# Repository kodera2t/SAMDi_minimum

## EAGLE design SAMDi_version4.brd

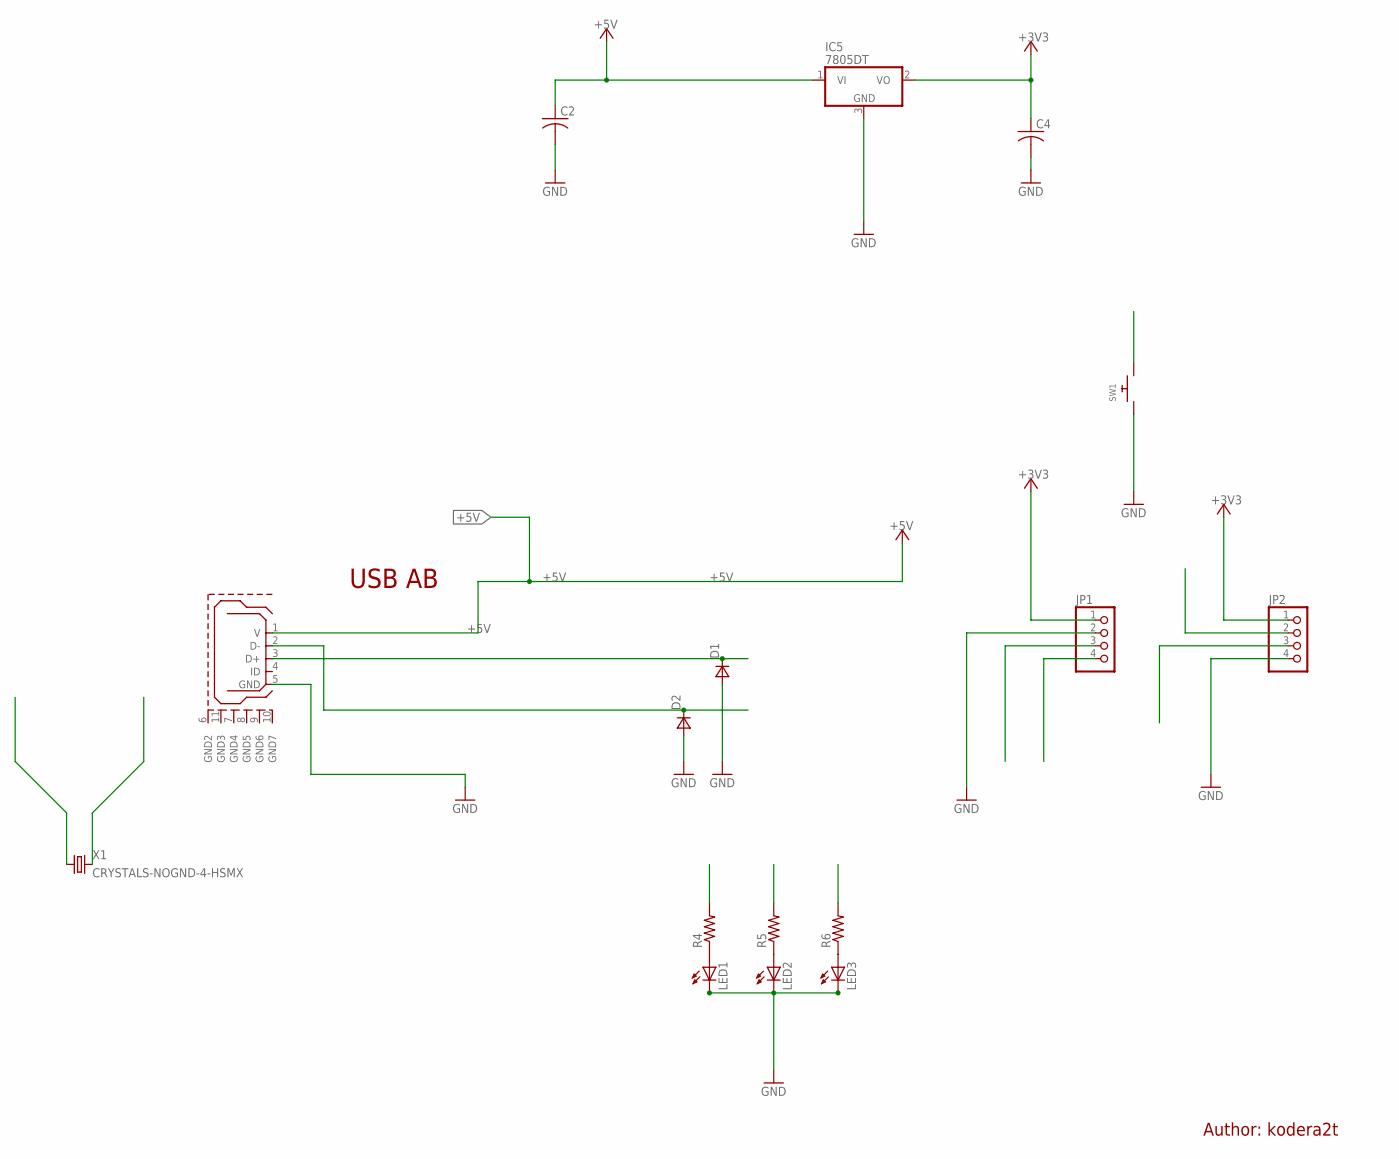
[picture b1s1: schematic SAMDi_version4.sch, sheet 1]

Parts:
C2, C4: C-USC0603; C0603
D1, D2: DSOD323; SOD323
IC5: 7805DT; TO252
JP1: HEADER-1X4; 1X04_OVAL
JP2: PINHD-1X4; 1X04
LED1, LED2, LED3: LEDCHIP-LED0603; CHIP-LED0603
R4, R5, R6: R-US_R0603; R0603
SW1: SWITCH_PUSHBUTTONSOFTTOUCHSMD_SJ; PUSHBUTTON_SMD_SJ
U$1: USB_MICROB; USB_MICROB_PACKAGE
X1: CRYSTALS-NOGND-4-HSMX; HC49-4-HSMX

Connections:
+3V3: C4.1, IC5.2 (VO), JP1.1, JP2.1; also elsewhere on the board
+5V: C2.1, IC5.1 (VI), U$1.1 (V)
GND: C2.2, C4.2, D1.2 (A), D2.2 (A), IC5.3 (GND), JP1.2, JP2.4, LED1.C, LED2.C, LED3.C, SW1.P$1, U$1.5 (GND); also elsewhere on the board
LED1: R4.2; also elsewhere on the board
LED2: R5.2; also elsewhere on the board
LED3: R6.2; also elsewhere on the board
unnamed: LED1.A, R4.1
unnamed: LED2.A, R5.1
unnamed: LED3.A, R6.1
RX: JP2.3; also elsewhere on the board
SCL: JP1.3; also elsewhere on the board
SDA: JP1.4; also elsewhere on the board
SWITCH1: SW1.P$2; also elsewhere on the board
TARGET_USB_N: D2.1 (C), U$1.2 (D-); also elsewhere on the board
TARGET_USB_P: D1.1 (C), U$1.3 (D+); also elsewhere on the board
TX: JP2.2; also elsewhere on the board
XTAL11: X1.2; also elsewhere on the board
XTAL22: X1.1; also elsewhere on the board

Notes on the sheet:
USB AB
Author: kodera2t

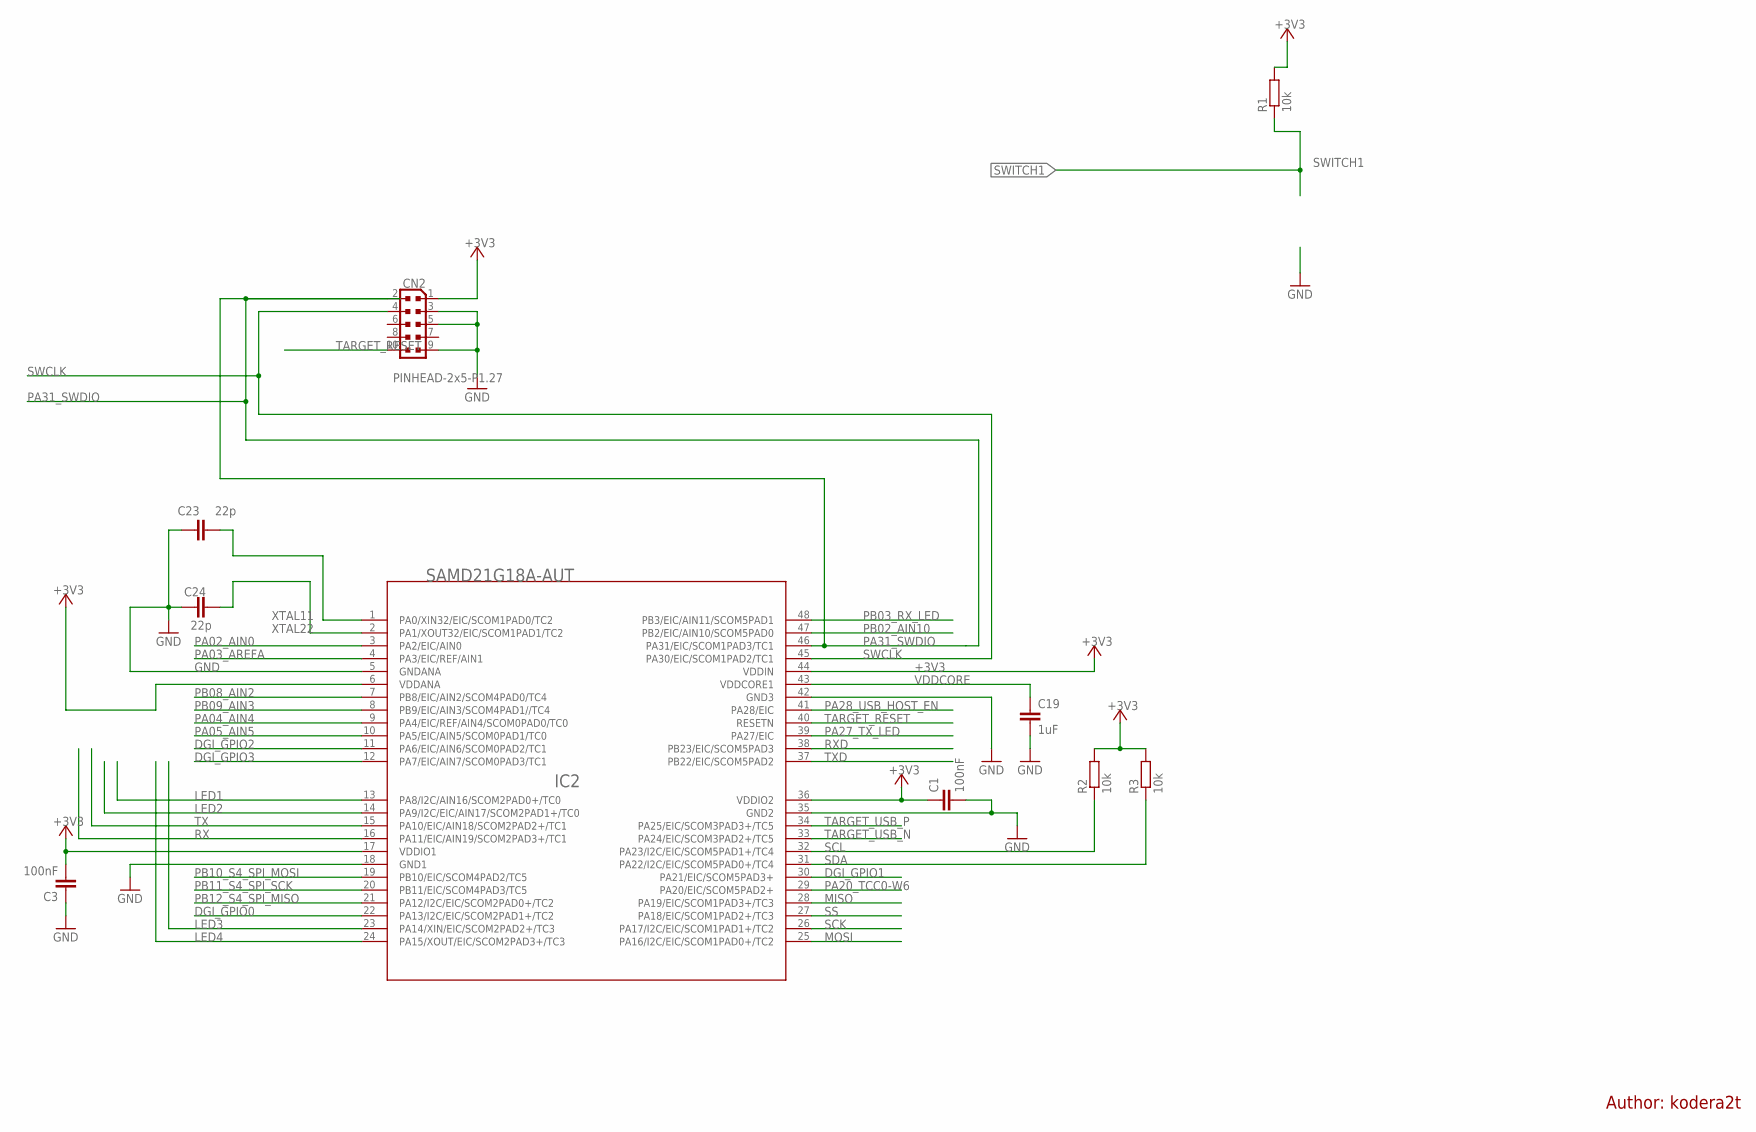
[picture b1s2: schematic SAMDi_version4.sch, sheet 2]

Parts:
C1, C3: 100nF; C0603-ROUND
C19: 1uF; C0603-ROUND
C23, C24: 22p; C0603-ROUND
CN2: PINHEAD-2x5-P1.27; PINHEAD_2X05_127
IC2: SAMD21G18A-AUT; TQFP48-7X7
R1, R2, R3: 10k; R0603-ROUND

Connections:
+3V3: C1.1, C3.2, CN2.1, IC2.6 (VDDANA), IC2.17 (VDDIO1), IC2.36 (VDDIO2), IC2.44 (VDDIN), R1.2, R2.2, R3.2; also elsewhere on the board
DGI_GPIO0: IC2.22 (PA13/I2C/EIC/SCOM2PAD1+/TC2)
DGI_GPIO1: IC2.30 (PA21/EIC/SCOM5PAD3+)
DGI_GPIO2: IC2.11 (PA6/EIC/AIN6/SCOM0PAD2/TC1)
DGI_GPIO3: IC2.12 (PA7/EIC/AIN7/SCOM0PAD3/TC1)
GND: C1.2, C3.1, C19.2, C23.1, C24.1, CN2.3, CN2.5, CN2.9, IC2.5 (GNDANA), IC2.18 (GND1), IC2.35 (GND2), IC2.42 (GND3); also elsewhere on the board
LED1: IC2.13 (PA8/I2C/AIN16/SCOM2PAD0+/TC0); also elsewhere on the board
LED2: IC2.14 (PA9/I2C/EIC/AIN17/SCOM2PAD1+/TC0); also elsewhere on the board
LED3: IC2.23 (PA14/XIN/EIC/SCOM2PAD2+/TC3); also elsewhere on the board
LED4: IC2.24 (PA15/XOUT/EIC/SCOM2PAD3+/TC3)
MISO: IC2.28 (PA19/EIC/SCOM1PAD3+/TC3)
MOSI: IC2.25 (PA16/I2C/EIC/SCOM1PAD0+/TC2)
PA02_AIN0: IC2.3 (PA2/EIC/AIN0)
PA03_AREFA: IC2.4 (PA3/EIC/REF/AIN1)
PA04_AIN4: IC2.9 (PA4/EIC/REF/AIN4/SCOM0PAD0/TC0)
PA05_AIN5: IC2.10 (PA5/EIC/AIN5/SCOM0PAD1/TC0)
PA20_TCC0-W6: IC2.29 (PA20/EIC/SCOM5PAD2+)
PA27_TX_LED: IC2.39 (PA27/EIC)
PA28_USB_HOST_EN: IC2.41 (PA28/EIC)
PA31_SWDIO: CN2.2, IC2.46 (PA31/EIC/SCOM1PAD3/TC1)
PB02_AIN10: IC2.47 (PB2/EIC/AIN10/SCOM5PAD0)
PB03_RX_LED: IC2.48 (PB3/EIC/AIN11/SCOM5PAD1)
PB08_AIN2: IC2.7 (PB8/EIC/AIN2/SCOM4PAD0/TC4)
PB09_AIN3: IC2.8 (PB9/EIC/AIN3/SCOM4PAD1//TC4)
PB10_S4_SPI_MOSI: IC2.19 (PB10/EIC/SCOM4PAD2/TC5)
PB11_S4_SPI_SCK: IC2.20 (PB11/EIC/SCOM4PAD3/TC5)
PB12_S4_SPI_MISO: IC2.21 (PA12/I2C/EIC/SCOM2PAD0+/TC2)
RX: IC2.16 (PA11/EIC/AIN19/SCOM2PAD3+/TC1); also elsewhere on the board
RXD: IC2.38 (PB23/EIC/SCOM5PAD3)
SCK: IC2.26 (PA17/I2C/EIC/SCOM1PAD1+/TC2)
SCL: IC2.32 (PA23/I2C/EIC/SCOM5PAD1+/TC4), R2.1; also elsewhere on the board
SDA: IC2.31 (PA22/I2C/EIC/SCOM5PAD0+/TC4), R3.1; also elsewhere on the board
SS: IC2.27 (PA18/EIC/SCOM1PAD2+/TC3)
SWCLK: CN2.4, IC2.45 (PA30/EIC/SCOM1PAD2/TC1)
SWITCH1: R1.1; also elsewhere on the board
TARGET_RESET: CN2.10, IC2.40 (RESETN)
TARGET_USB_N: IC2.33 (PA24/EIC/SCOM3PAD2+/TC5); also elsewhere on the board
TARGET_USB_P: IC2.34 (PA25/EIC/SCOM3PAD3+/TC5); also elsewhere on the board
TX: IC2.15 (PA10/EIC/AIN18/SCOM2PAD2+/TC1); also elsewhere on the board
TXD: IC2.37 (PB22/EIC/SCOM5PAD2)
VDDCORE: C19.1, IC2.43 (VDDCORE1)
XTAL11: C23.2, IC2.1 (PA0/XIN32/EIC/SCOM1PAD0/TC2); also elsewhere on the board
XTAL22: C24.2, IC2.2 (PA1/XOUT32/EIC/SCOM1PAD1/TC2); also elsewhere on the board

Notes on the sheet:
Author: kodera2t

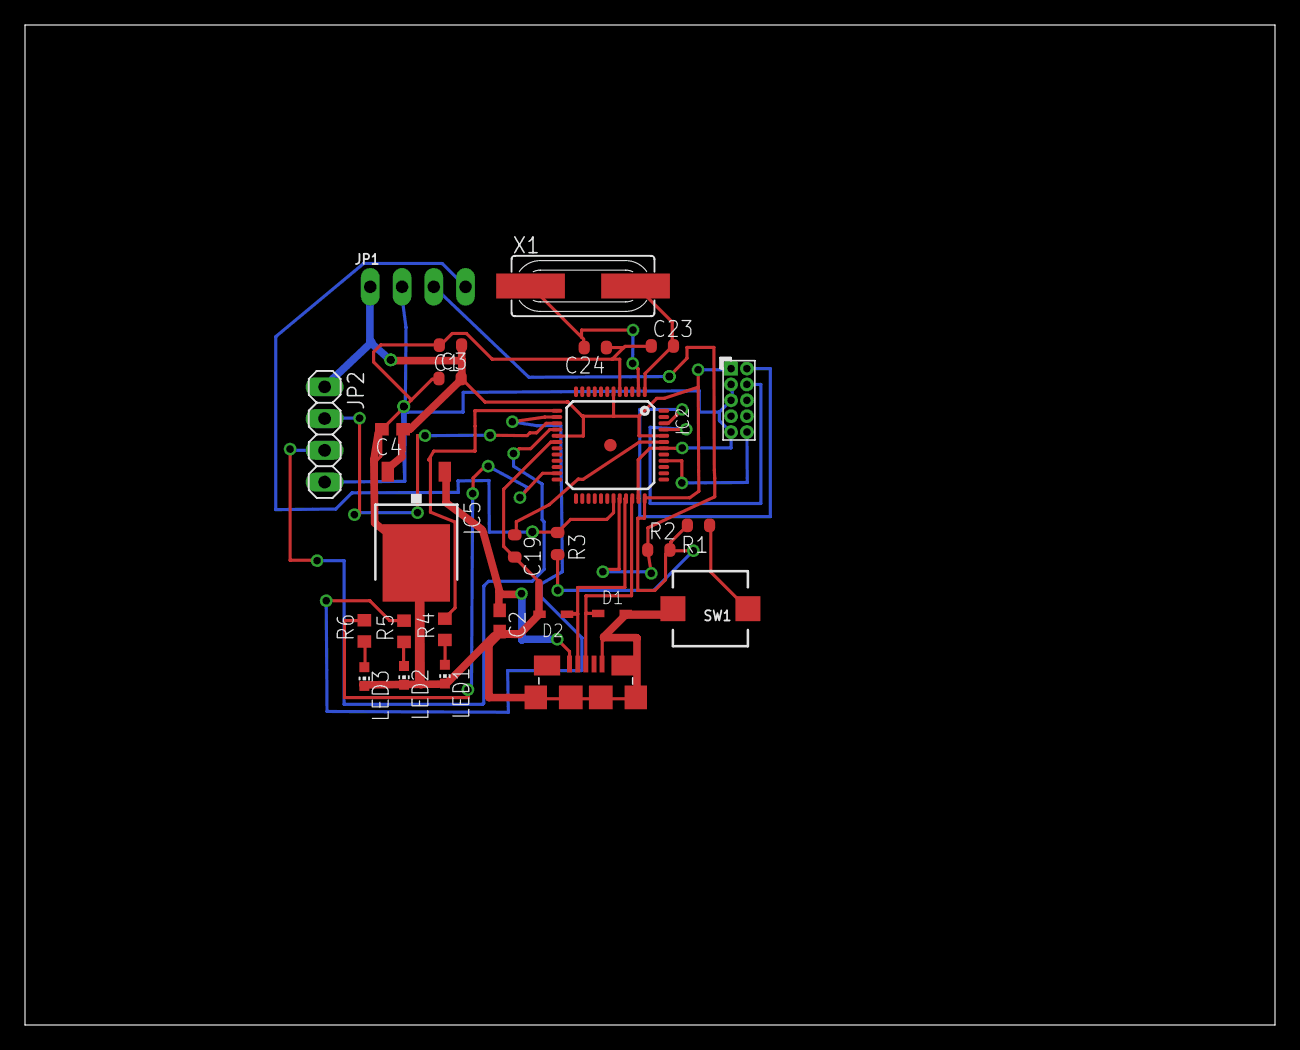
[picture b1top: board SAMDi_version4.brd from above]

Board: 2 copper layers, 100.0 x 80.0 mm, 26 parts (0 on the bottom side), 22 nets.

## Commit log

2015-08-20 initial submission

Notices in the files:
parts and their libraries:
microbuilder: This work is placed in the public domain, and may be freely used for commercial and non-commercial work with the following conditions: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
